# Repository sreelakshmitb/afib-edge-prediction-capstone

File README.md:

# AFib edge prediction capstone

**AI-Based Single-Lead ECG Monitoring System for Early Atrial Fibrillation Prediction Using Edge Computing**

A research prototype that uses ten minutes of single-lead ECG to estimate AF onset risk within the following twenty minutes. MAX30003 acquisition and ESP32 Wi-Fi transport feed a Raspberry Pi 4B, which runs preprocessing and the frozen ONNX forecaster and serves an Android application.

## Final project

| Item | Published implementation |
| --- | --- |
| Model | SE-CNN-HRV-UniLSTM, GroupNorm/curriculum, 159,503 parameters |
| Frozen checkpoint | [forecast_checkpoint.pt](artifacts/frozen_forecast_v1/forecast_checkpoint.pt) |
| Pi graph and preprocessing | [deployment/pi/model](deployment/pi/model) |
| Model source and recipe | [training/unified](training/unified), `build_model("proposed-groupnorm")` |
| Model input | 250 Hz; ECG `[B,20,1,7500]`; HRV `[B,20,6]` |
| Output | One logit; sigmoid score; validation-selected cutoff **0.3310546875** |
| Pi receiver, inference and app bridge | [deployment/pi](deployment/pi) |
| Android | [android](android), imported v1.4.8 live-resume source |
| ESP32 | [live Wi-Fi firmware](firmware/afib_live_wifi/afib_live_wifi.ino) |
| PCB | [Rev B KiCad, fabrication and mechanical files](hardware/pcb) |
| Integrity | [SHA-256 release manifest](artifacts/RELEASE_MANIFEST.json) |

## Results for the frozen model

The once-only patient-disjoint outer fold-0 test contains **1,809 windows**, including 236 positives. AP is **0.22175**, AUROC **0.66424**, recall **23.31%**, and specificity **90.97%** at the frozen threshold. Confusion counts: TP 55, FN 181, FP 142, TN 1,431. It detected 38/107 eligible events, including 9/48 events in the 16–20 minute lead band.

These are modest research results with limited sensitivity. A below-threshold score does not rule out AF. This is a research prototype, not a validated diagnostic device.

The later fivefold BCE development assessment uses different checkpoints. See [results and limitations](docs/RESULTS.md), [raw test summary](results/frozen_forecast_sealed_test_v1/summary.json), and [predictions](results/frozen_forecast_sealed_test_v1/test_predictions.csv).

## Start here

1. [Pi setup and live/replay commands](deployment/pi/README.md)
2. [Model card and loading](docs/FINAL_MODEL.md)
3. [Datasets and experiment scope](docs/DATASETS.md)
4. [Training and notebooks](training/README.md)
5. [Hardware and firmware](hardware/README.md)
6. [Current state and remaining evidence](PROJECT_STATE.md)
7. [Import provenance and cleanup](docs/RELEASE_NOTES_2026-11-20.md)

Live mode collects a real ten minutes before its first forecast. Replay transfers a prerecorded ten-minute waveform faster than real time. Presentation simulation is a UI demonstration and must be off for actual Pi inference.

## Verification

```bash
python scripts/verify_release.py
python -m pip install -r deployment/pi/requirements.txt
python scripts/verify_frozen_model.py
```

The first command verifies published hashes without ML dependencies. The model check executes ONNX on three supplied validation fixtures. Add `--checkpoint` after installing PyTorch to compare both runtimes.

## Project team and attribution

Joint work of [Sreelakshmi T B](https://github.com/sreelakshmitb), [Jagadjith U](https://github.com/Jagadjith-U), and [Aravind V S](https://github.com/aravindd3). Research, software, experiments, analysis and documentation were collaborative; commit authorship records who uploaded a change.

The CNN-HRV-UniLSTM direction is based on the Zhang et al. reference documented in [the reproducibility audit](docs/PAPER_REPRODUCIBILITY_AUDIT.md). SE attention, training repairs, eligibility work and device integration are capstone work; no superiority from SE alone is claimed.

The earlier `afib/`, `src/`, `configs/`, tests and `model_bundles/se_last_mask_seed7/` remain historical development material. Their checkpoints and preprocessing are not interchangeable with the frozen deployment. No complete raw dataset is included; deployment includes three small validation fixtures from the supplied export.

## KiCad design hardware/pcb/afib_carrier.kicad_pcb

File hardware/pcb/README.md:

# AFIB Carrier Rev B — Prototype Fabrication Candidate

This project is the small-batch prototype candidate derived from the uploaded
Rev A archive. Open `afib_carrier.kicad_pro` in KiCad 10.

## Release checks

- KiCad 10.0.6 PCB DRC: **0 violations**
- Unconnected PCB items: **0**
- Schematic/PCB parity issues: **0**
- Schematic ERC: **0 violations**
- Minimum track: 0.25 mm
- Minimum via drill: 0.30 mm
- Minimum configured copper clearance: 0.20 mm
- Minimum configured copper-to-edge clearance: 0.50 mm
- ESP32 antenna keepout coordinates checked after save/reload
- Battery B− remains separate from charger OUT−/system GND

## Board specification

- 90.00 × 80.00 mm, 1.60 mm FR-4
- Two copper layers, 1 oz copper recommended
- R2 mm corners
- Four Ø3.20 mm NPTH mounting holes at (4,4), (86,4), (4,76),
  (86,76) mm from the top-left drawing origin
- Lead-free HASL is sufficient; ENIG is optional
- Order 2–5 boards first and electrically test one fully before a larger batch

## BO-10186 footprint used

The supplied listing screenshots state **2.54 mm pitch** and **20 × 15 × 5 mm**.
The carrier therefore uses a normal 1×4 2.54 mm through-hole pattern with
1.0 mm plated drills and a conservative 20 × 15 mm reserved body envelope.
The header centreline is placed 1.27 mm from the reserved left edge, matching
the product photographs. The complete envelope is inside the carrier outline.

Top-to-bottom at U3:

| Pad | Module marking | Net | Board XY, mm |
|---|---|---|---|
| 1 | VOUT | +3V3 | 69.47, 57.00 |
| 2 | GND | GND | 69.47, 59.54 |
| 3 | GND | GND | 69.47, 62.08 |
| 4 | VIN | REG_IN_POS | 69.47, 64.62 |

Pad 1 is square. Fit the module with its component side upward and body extending
to the right of the header. If the supplied module differs from the listing,
the same four labelled carrier pads can be connected using short insulated wires;
do not force a mismatched module into a rigid socket.

## MAX30003 socket

The eight-pin digital header uses 2.54 mm pitch. The supplied photograph confirms
the order. All pads are at X36.00 mm; from top to bottom:

| Pad | Net | Y, mm |
|---|---|---|
| 8 | ECG_INTB | 37.22 |
| 7 | ECG_INT2B | 39.76 |
| 6 | SPI_MISO | 42.30 |
| 5 | SPI_MOSI | 44.84 |
| 4 | SPI_SCK | 47.38 |
| 3 | ECG_CS | 49.92 |
| 2 | +3V3 / VCC | 52.46 |
| 1 | GND | 55.00 |

The daughterboard body extends left, with the ECG jack/cable toward the left
edge. Its body and cable area uses a conservative reservation. Check the first
assembled board and keep the enclosure opening adjustable.

## Manufacturing files

The `fabrication/` folder contains Gerbers, separate PTH/NPTH Excellon files,
drill map/report, schematic PDF, fabrication notes and the final DRC/ERC reports.
Gerbers include copper, solder mask, silkscreen, paste and board outline layers.

Do not panelize, alter the outline or merge the NPTH file into plated drills
without confirming the four mounting holes remain non-plated.

## First-article electrical test

1. Inspect for shorts and connector reversal before fitting modules.
2. Fit only the power input, switch and BO-10186.
3. Use a current-limited supply in place of the cell and confirm 3.3 V polarity.
4. Check regulator heating and supply droop over the intended battery range.
5. Fit the ESP32 and test BLE current bursts.
6. Fit the SD socket/card and test repeated writes while monitoring 3.3 V.
7. Fit the MAX30003 last and confirm SPI/interrupt operation before electrodes.

This is a research/evaluation prototype. It is not a certified medical device
or patient-isolated system. Disconnect electrodes during charging, USB/UART
programming or any mains-connected measurement. Use battery power while a
person is connected. Have the assembled electrode-input protection reviewed
before body-connected testing, and do not infer ECGP/ECGN/VCM from cable colours.

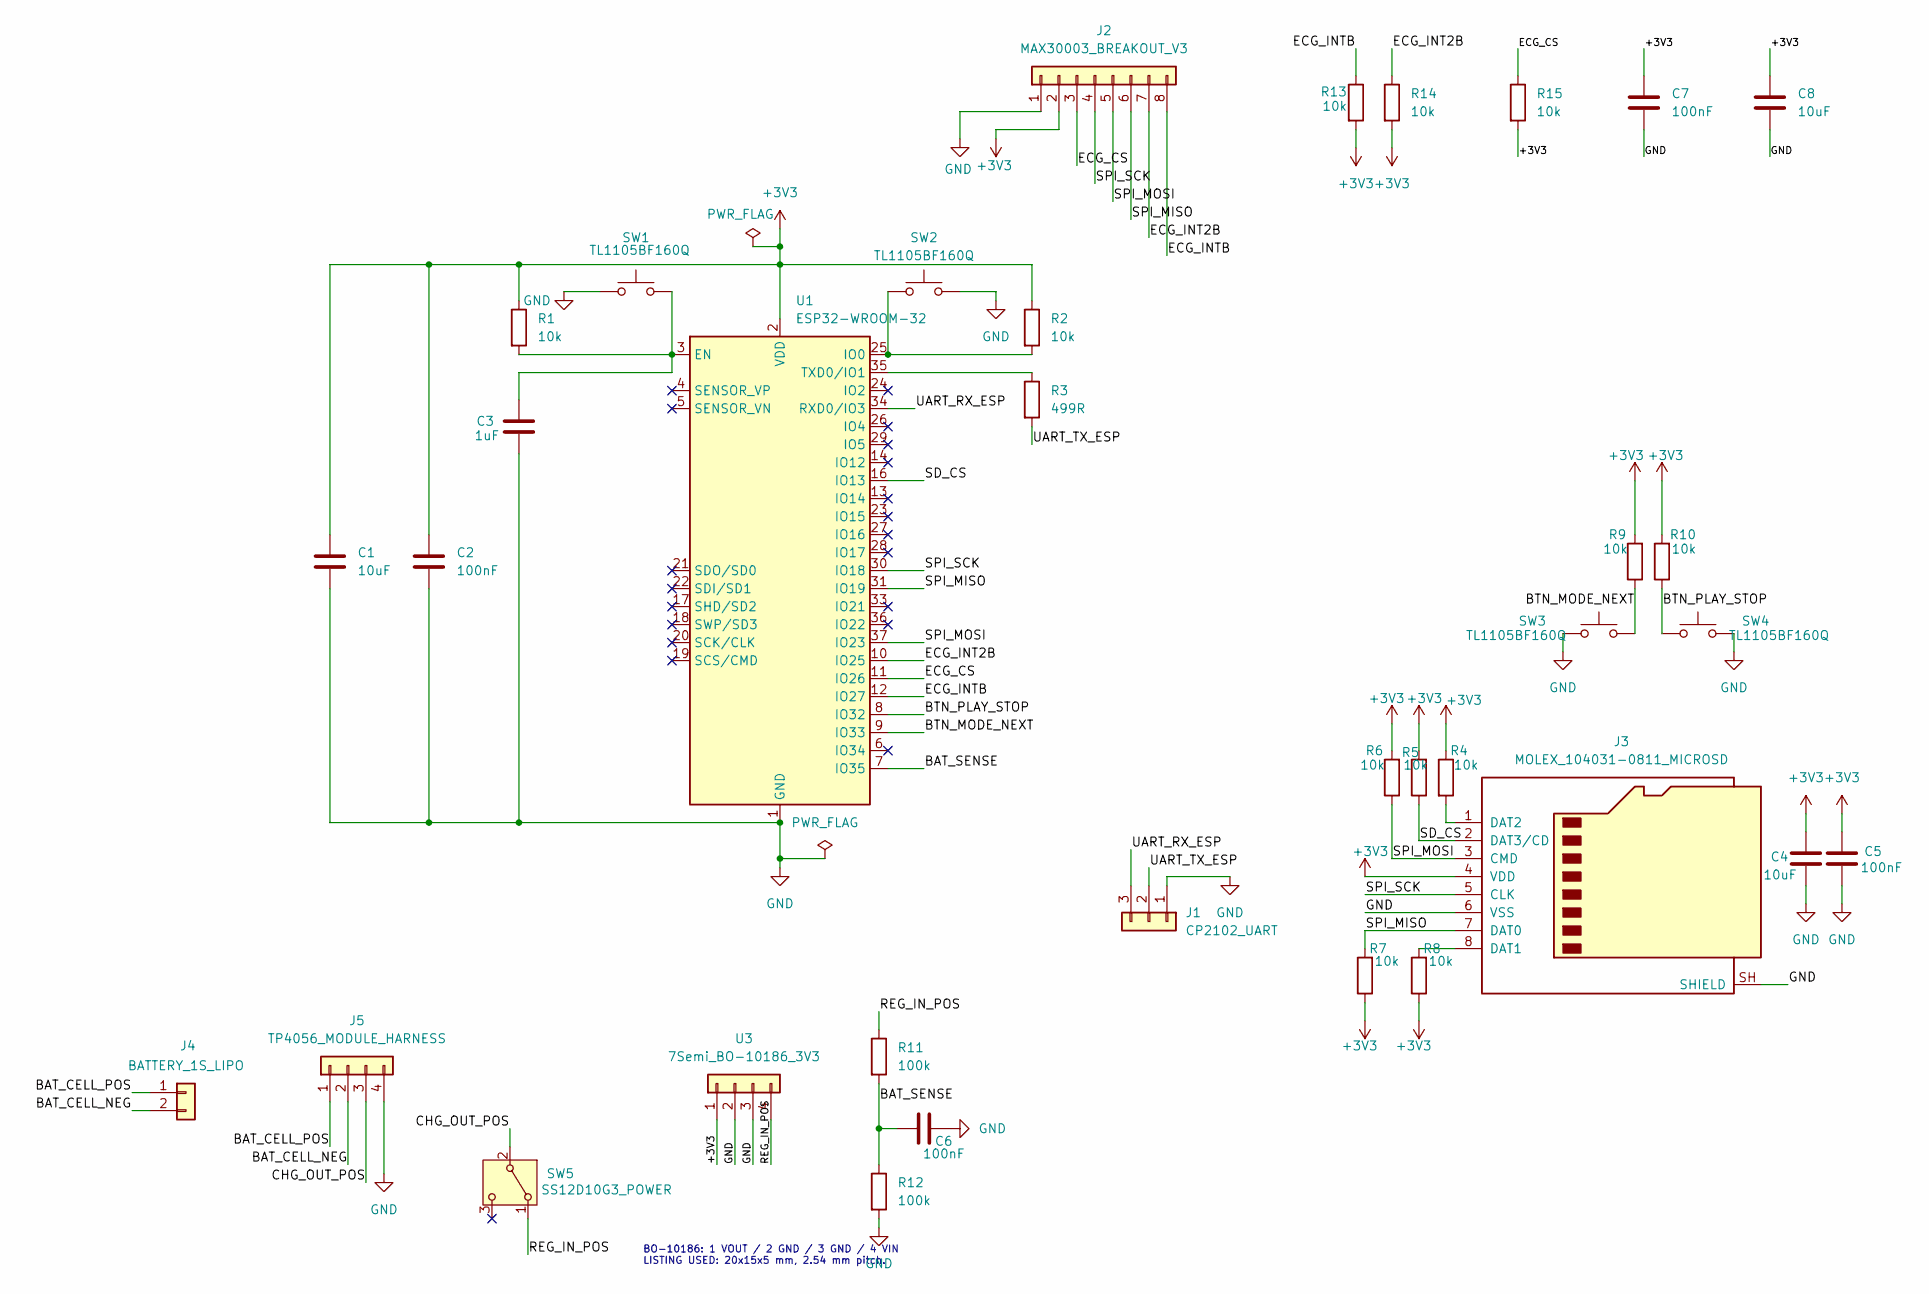
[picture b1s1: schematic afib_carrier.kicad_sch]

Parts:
C1, C4, C8: 10uF; C_0805_2012Metric_Pad1.18x1.45mm_HandSolder
C2, C5, C6, C7: 100nF; C_0805_2012Metric_Pad1.18x1.45mm_HandSolder
C3: 1uF; C_0805_2012Metric_Pad1.18x1.45mm_HandSolder
J1: CP2102_UART; PinHeader_1x03_P2.54mm_Vertical
J2: MAX30003_BREAKOUT_V3; MAX30003_V3_Socket_Envelope_Provisional
J3: MOLEX_104031-0811_MICROSD; microSD_HC_Molex_104031-0811
J4: BATTERY_1S_LIPO; JST_PH_B2B-PH-K_1x02_P2.00mm_Vertical
J5: TP4056_MODULE_HARNESS; JST_PH_B4B-PH-K_1x04_P2.00mm_Vertical
R1, R2, R4, R5, R6, R7, R8, R9, R10, R13, R14, R15: 10k; R_0805_2012Metric_Pad1.20x1.40mm_HandSolder
R3: 499R; R_0805_2012Metric_Pad1.20x1.40mm_HandSolder
R11, R12: 100k; R_0805_2012Metric_Pad1.20x1.40mm_HandSolder
SW1, SW2, SW3, SW4: TL1105BF160Q; SW_PUSH_6mm
SW5: SS12D10G3_POWER; SS12D10G3_Power
U1: ESP32-WROOM-32; ESP32_WROOM32_0p30mm_thermal
U3: 7Semi_BO-10186_3V3; 7Semi_BO10186_P2.54_20x15

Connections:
+3V3: C1.1, C2.1, C4.1, C5.1, C7.1, C8.1, J2.2, J3.4 (VDD), R1.1, R2.1, R4.1, R5.2, R6.2, R7.1, R8.1, R9.2, R10.2, R13.2, R14.2, R15.2, U1.2 (VDD), U3.1
/BAT_CELL_NEG: J4.2, J5.2
/BAT_CELL_POS: J4.1, J5.1
/BAT_SENSE: C6.2, R11.2, R12.1, U1.7 (IO35)
/BTN_MODE_NEXT: R9.1, SW3.2, U1.9 (IO33)
/BTN_PLAY_STOP: R10.1, SW4.1, U1.8 (IO32)
/CHG_OUT_POS: J5.3, SW5.2 (B)
/ECG_CS: J2.3, R15.1, U1.11 (IO26)
/ECG_INT2B: J2.7, R14.1, U1.10 (IO25)
/ECG_INTB: J2.8, R13.1, U1.12 (IO27)
/REG_IN_POS: R11.1, SW5.1 (A), U3.4
/SD_CS: J3.2 (DAT3/CD), R5.1, U1.16 (IO13)
/SPI_MISO: J2.6, J3.7 (DAT0), R7.2, U1.31 (IO19)
/SPI_MOSI: J2.5, J3.3 (CMD), R6.1, U1.37 (IO23)
/SPI_SCK: J2.4, J3.5 (CLK), U1.30 (IO18)
/UART_RX_ESP: J1.3, U1.34 (RXD0/IO3)
/UART_TX_ESP: J1.2, R3.2
GND: C1.2, C2.2, C3.2, C4.2, C5.2, C6.1, C7.2, C8.2, J1.1, J2.1, J3.6 (VSS), J3.SH (SHIELD), J5.4, R12.2, SW1.2, SW2.2, SW3.1, SW4.2, U1.1 (GND), U1.15 (GND), U1.38 (GND), U1.39 (GND), U3.2, U3.3
unnamed: J3.8 (DAT1), R8.2
unnamed: J3.1 (DAT2), R4.2
unnamed: C3.1, R1.2, SW1.1, U1.3 (EN)
unnamed: R2.2, SW2.1, U1.25 (IO0)
unnamed: R3.1, U1.35 (TXD0/IO1)

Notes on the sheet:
BO-10186: 1 VOUT / 2 GND / 3 GND / 4 VIN LISTING USED: 20x15x5 mm, 2.54 mm pitch.

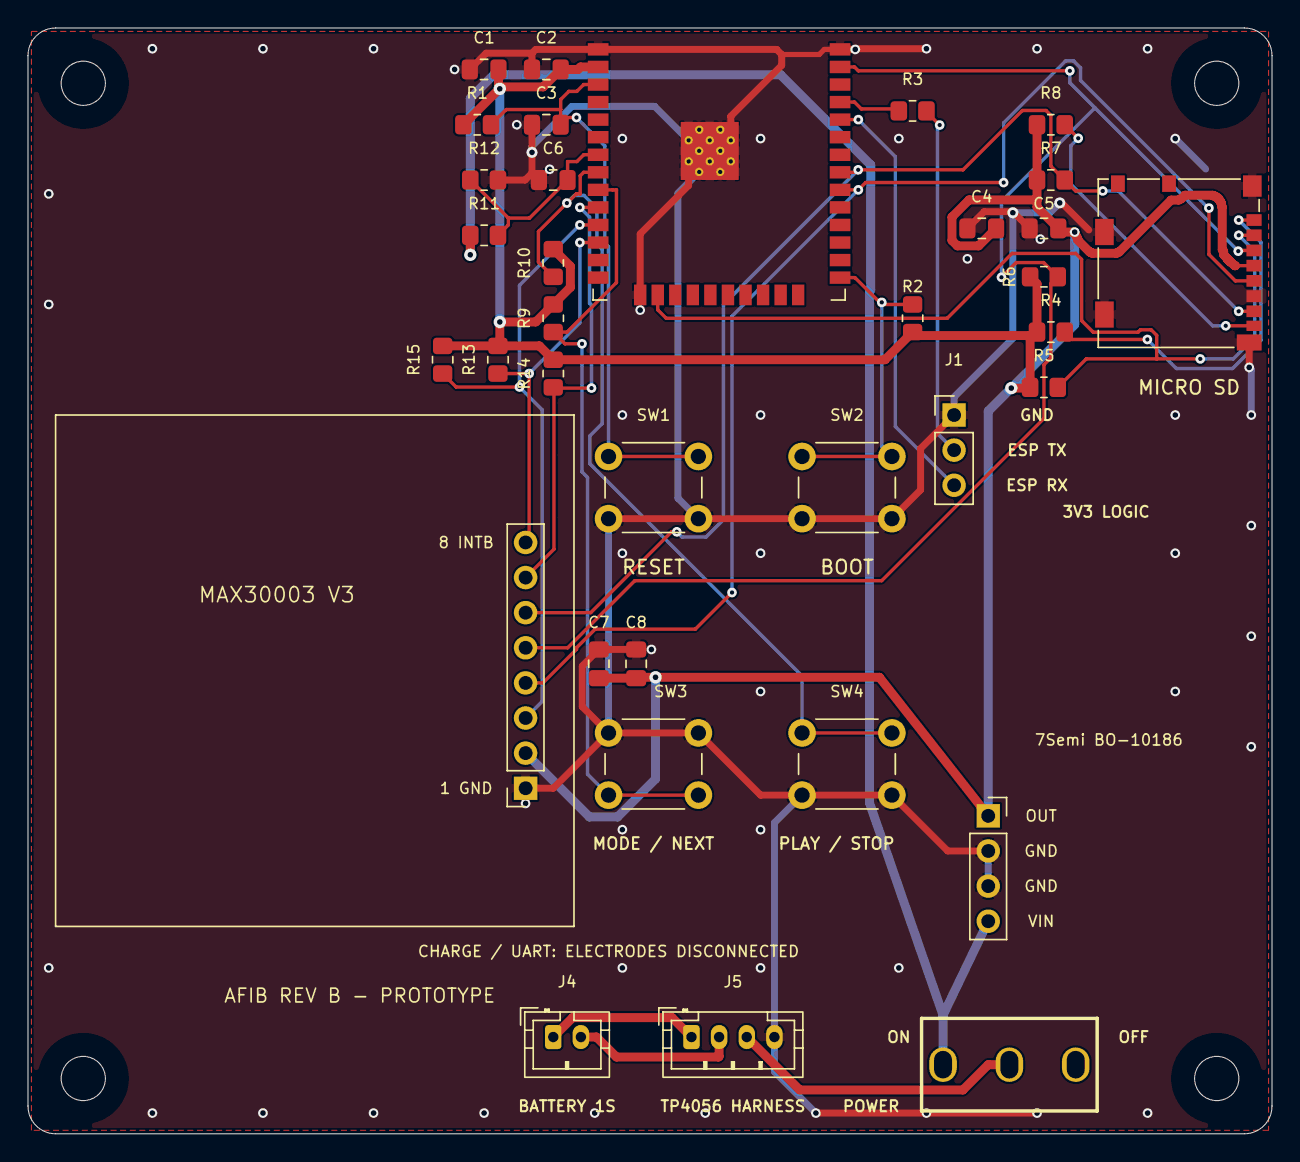
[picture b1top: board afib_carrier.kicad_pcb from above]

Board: 2 copper layers, 90.0 x 80.0 mm, 39 parts (0 on the bottom side), 23 nets.

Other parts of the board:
H1, H2, H3, H4: M3_NPTH; MountingHole_3.2mm_M3

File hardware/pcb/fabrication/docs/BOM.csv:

Reference,Value,Footprint,Notes
C1,10uF,Capacitor_SMD:C_0805_2012Metric_Pad1.18x1.45mm_HandSolder,Retained baseline part
C2,100nF,Capacitor_SMD:C_0805_2012Metric_Pad1.18x1.45mm_HandSolder,Retained baseline part
C3,1uF,Capacitor_SMD:C_0805_2012Metric_Pad1.18x1.45mm_HandSolder,Retained baseline part
C4,10uF,Capacitor_SMD:C_0805_2012Metric_Pad1.18x1.45mm_HandSolder,Retained baseline part
C5,100nF,Capacitor_SMD:C_0805_2012Metric_Pad1.18x1.45mm_HandSolder,Retained baseline part
C6,100nF,Capacitor_SMD:C_0805_2012Metric_Pad1.18x1.45mm_HandSolder,Retained baseline part
C7,100nF,Capacitor_SMD:C_0805_2012Metric_Pad1.18x1.45mm_HandSolder,Retained baseline part
C8,10uF,Capacitor_SMD:C_0805_2012Metric_Pad1.18x1.45mm_HandSolder,Retained baseline part
H1,M3_NPTH,MountingHole:MountingHole_3.2mm_M3,Retained baseline part
H2,M3_NPTH,MountingHole:MountingHole_3.2mm_M3,Retained baseline part
H3,M3_NPTH,MountingHole:MountingHole_3.2mm_M3,Retained baseline part
H4,M3_NPTH,MountingHole:MountingHole_3.2mm_M3,Retained baseline part
J1,CP2102_UART,Connector_PinHeader_2.54mm:PinHeader_1x03_P2.54mm_Vertical,Retained baseline part
J2,MAX30003_BREAKOUT_V3,Afib:MAX30003_V3_Socket_Envelope_Provisional,2.54 mm header; conservative 37.5 x 37 mm body reservation; verify first article fit
J3,MOLEX_104031-0811_MICROSD,Connector_Card:microSD_HC_Molex_104031-0811,Retained baseline part
J4,BATTERY_1S_LIPO,Connector_JST:JST_PH_B2B-PH-K_1x02_P2.00mm_Vertical,Retained baseline part
J5,TP4056_MODULE_HARNESS,Connector_JST:JST_PH_B4B-PH-K_1x04_P2.00mm_Vertical,Retained baseline part
R1,10k,Resistor_SMD:R_0805_2012Metric_Pad1.20x1.40mm_HandSolder,Retained baseline part
R10,10k,Resistor_SMD:R_0805_2012Metric_Pad1.20x1.40mm_HandSolder,Retained baseline part
R11,100k,Resistor_SMD:R_0805_2012Metric_Pad1.20x1.40mm_HandSolder,Retained baseline part
R12,100k,Resistor_SMD:R_0805_2012Metric_Pad1.20x1.40mm_HandSolder,Retained baseline part
R13,10k,Resistor_SMD:R_0805_2012Metric_Pad1.20x1.40mm_HandSolder,Retained baseline part
R14,10k,Resistor_SMD:R_0805_2012Metric_Pad1.20x1.40mm_HandSolder,Retained baseline part
R15,10k,Resistor_SMD:R_0805_2012Metric_Pad1.20x1.40mm_HandSolder,Retained baseline part
R2,10k,Resistor_SMD:R_0805_2012Metric_Pad1.20x1.40mm_HandSolder,Retained baseline part
R3,499R,Resistor_SMD:R_0805_2012Metric_Pad1.20x1.40mm_HandSolder,Retained baseline part
R4,10k,Resistor_SMD:R_0805_2012Metric_Pad1.20x1.40mm_HandSolder,Retained baseline part
R5,10k,Resistor_SMD:R_0805_2012Metric_Pad1.20x1.40mm_HandSolder,Retained baseline part
R6,10k,Resistor_SMD:R_0805_2012Metric_Pad1.20x1.40mm_HandSolder,Retained baseline part
R7,10k,Resistor_SMD:R_0805_2012Metric_Pad1.20x1.40mm_HandSolder,Retained baseline part
R8,10k,Resistor_SMD:R_0805_2012Metric_Pad1.20x1.40mm_HandSolder,Retained baseline part
R9,10k,Resistor_SMD:R_0805_2012Metric_Pad1.20x1.40mm_HandSolder,Retained baseline part
SW1,TL1105BF160Q,Button_Switch_THT:SW_PUSH_6mm,Retained baseline part
SW2,TL1105BF160Q,Button_Switch_THT:SW_PUSH_6mm,Retained baseline part
SW3,TL1105BF160Q,Button_Switch_THT:SW_PUSH_6mm,Retained baseline part
SW4,TL1105BF160Q,Button_Switch_THT:SW_PUSH_6mm,Retained baseline part
SW5,SS12D10G3_POWER,Afib:SS12D10G3_Power,Retained baseline part
U1,ESP32-WROOM-32,Afib:ESP32_WROOM32_0p30mm_thermal,Retained baseline part
U3,7Semi_BO-10186_3V3,Afib:7Semi_BO10186_P2.54_20x15,BO-10186 listing applied: 2.54 mm pitch and 20 x 15 x 5 mm envelope
